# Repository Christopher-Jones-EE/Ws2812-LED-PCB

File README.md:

# RGB LED Mood Light PCB

**Description:**  
USB-powered RGB LED mood light using an ATmega328P microcontroller. Designed to control multiple WS2812B LEDs with smooth color transitions.

**Hardware:**  
- ATmega328P microcontroller  
- WS2812B LEDs  
- PCB designed in KiCad  
- Arduino Uno (used for bootloading)
- FTDI breakout board for uploading code 

**Software:**  
- Arduino IDE (C++)  

**Features:**  
- Smooth PWM-based color transitions  
- Custom PCB integrates microcontroller for compact design  
- Modular programming via FTDI interface  

**Project Highlights:**  
- Designed complete schematic and PCB layout from scratch  
- Bootloaded ATmega328P using Arduino Uno  
- Implemented stable, low-latency LED control  

**Files Included:**  
- KiCad schematic and PCB files (`.sch`, `.kicad_pcb`)

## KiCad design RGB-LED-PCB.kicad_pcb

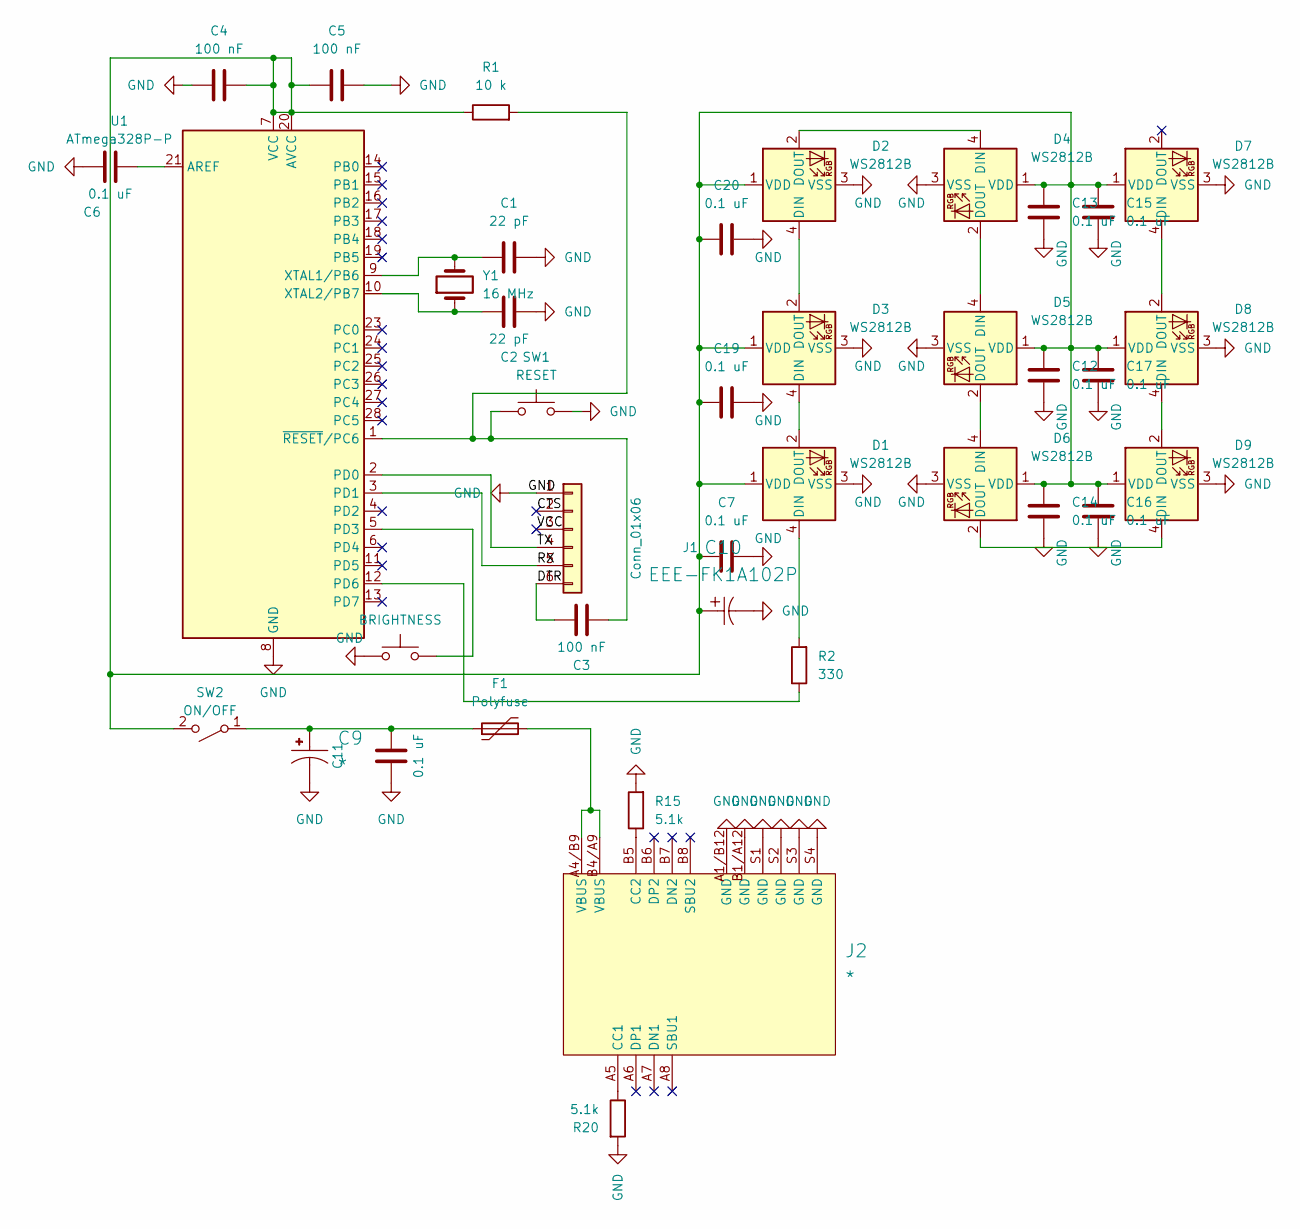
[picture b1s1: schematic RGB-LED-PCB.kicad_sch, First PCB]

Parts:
C1, C2: 22 pF; CAP_CL21_SAM
C3, C4, C5: 100 nF; CAPC220145_88N_KEM
C6, C7, C11, C12, C13, C14, C15, C16, C17, C19, C20: 0.1 uF; CAPC220145_88N_KEM
C9: *; CAPPRD350W60D800H1150
C10: EEE-FK1A102P; CAP_EEFK_G_PAN; Manufacturer_Part_Number EEE-FK1A102P
D1, D2, D3, D4, D5, D6, D7, D8, D9: WS2812B; COM-16347_SPK
F1: Polyfuse; 0ZCG_BEL
J1: Conn_01x06; SULLINS_PPTC061LFBN-RC
J2: *; GCT_USB4110GFA
R1: 10 k; STA_RMCF0805_STP
R2: 330; RESC2012X60N
R15, R20: 5.1k; RESC2012X60N
SW1: RESET; SON4_PTS526 SM15 SMTR2 LFS_CNK
SW2: ON/OFF; SW_S101031MS02Q
SW3: BRIGHTNESS; SON4_PTS526 SM15 SMTR2 LFS_CNK
U1: ATmega328P-P; DIP794W46P254L2967H457Q28B
Y1: 16 MHz; XTAL_HCM49_CIT

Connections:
/CTS: J1.2
/DTR: C3.1, J1.6
/RX: J1.5, U1.3 (PD1)
/TX: J1.4, U1.2 (PD0)
/VCC: J1.3
GND: C1.2, C2.2, C4.1, C5.2, C6.1, C7.1, C9.N, C10.2, C11.1, C12.1, C13.1, C14.1, C15.1, C16.1, C17.1, C19.1, C20.1, D1.3 (VSS), D2.3 (VSS), D3.3 (VSS), D4.3 (VSS), D5.3 (VSS), D6.3 (VSS), D7.3 (VSS), D8.3 (VSS), D9.3 (VSS), J1.1, J2.A1/B12 (GND), J2.B1/A12 (GND), J2.S1 (GND), J2.S2 (GND), J2.S3 (GND), J2.S4 (GND), R15.2, R20.2, SW1.2, SW3.1, U1.8 (GND), U1.22 (GND)
unnamed: D1.4 (DIN), R2.2
unnamed: D1.2 (DOUT), D3.4 (DIN)
unnamed: C4.2, C5.1, C7.2, C10.1, C12.2, C13.2, C14.2, C15.2, C16.2, C17.2, C19.2, C20.2, D1.1 (VDD), D2.1 (VDD), D3.1 (VDD), D4.1 (VDD), D5.1 (VDD), D6.1 (VDD), D7.1 (VDD), D8.1 (VDD), D9.1 (VDD), R1.1, SW2.2 (B), U1.7 (VCC), U1.20 (AVCC)
unnamed: D2.4 (DIN), D3.2 (DOUT)
unnamed: D2.2 (DOUT), D4.4 (DIN)
unnamed: D4.2 (DOUT), D5.4 (DIN)
unnamed: D5.2 (DOUT), D6.4 (DIN)
unnamed: D6.2 (DOUT), D9.4 (DIN)
unnamed: D7.4 (DIN), D8.2 (DOUT)
unnamed: D8.4 (DIN), D9.2 (DOUT)
unnamed: F1.2, J2.A4/B9 (VBUS), J2.B4/A9 (VBUS)
unnamed: J2.A5 (CC1), R20.1
unnamed: J2.B5 (CC2), R15.1
unnamed: C9.P, C11.2, F1.1, SW2.1 (A)
unnamed: C6.2, U1.21 (AREF)
unnamed: SW3.2, U1.5 (PD3)
unnamed: R2.1, U1.12 (PD6)
unnamed: C1.1, U1.9 (XTAL1/PB6), Y1.2
unnamed: C2.1, U1.10 (XTAL2/PB7), Y1.1
unnamed: C3.2, R1.2, SW1.1, U1.1 (~RESET/PC6)

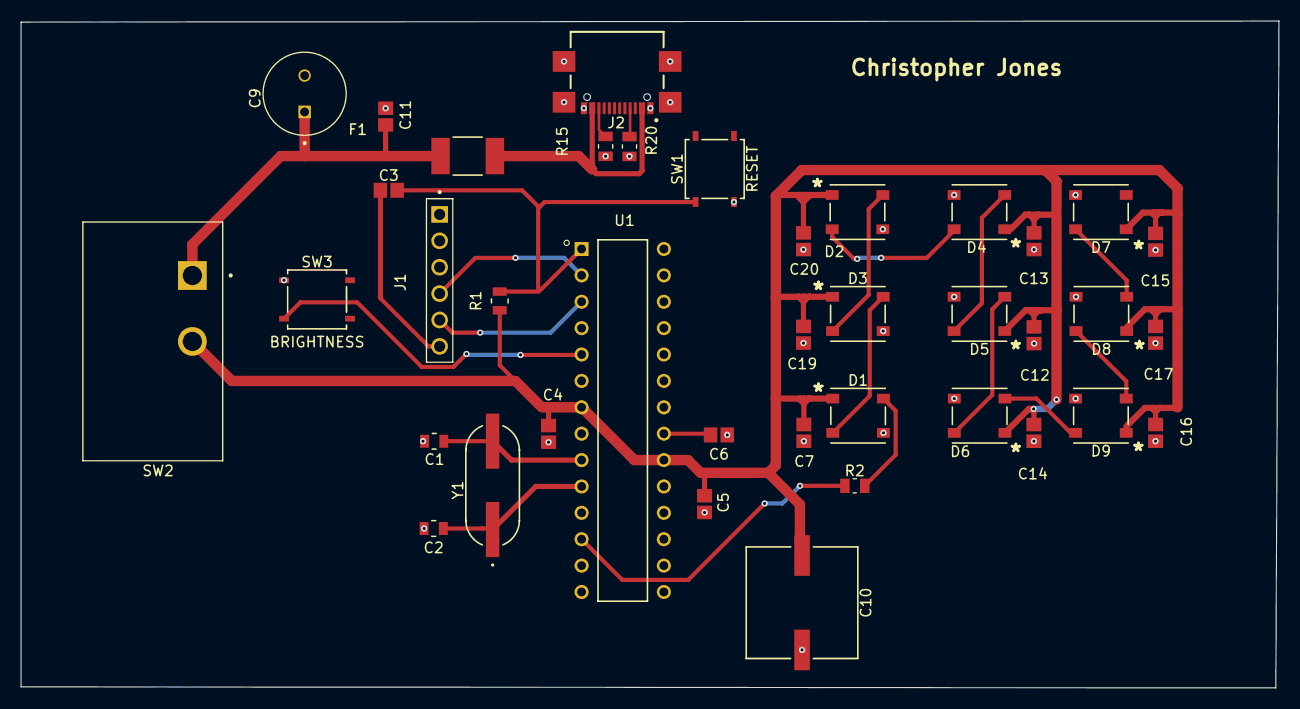
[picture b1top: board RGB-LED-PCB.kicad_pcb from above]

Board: 2 copper layers, 121.1 x 64.2 mm, 39 parts (0 on the bottom side), 24 nets.

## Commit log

2026-01-14 Rename IMG_7175.MOV to Video

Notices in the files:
parts and their libraries:
Copyright: Copyright (C) 2025 Ultra Librarian. All rights reserved.
